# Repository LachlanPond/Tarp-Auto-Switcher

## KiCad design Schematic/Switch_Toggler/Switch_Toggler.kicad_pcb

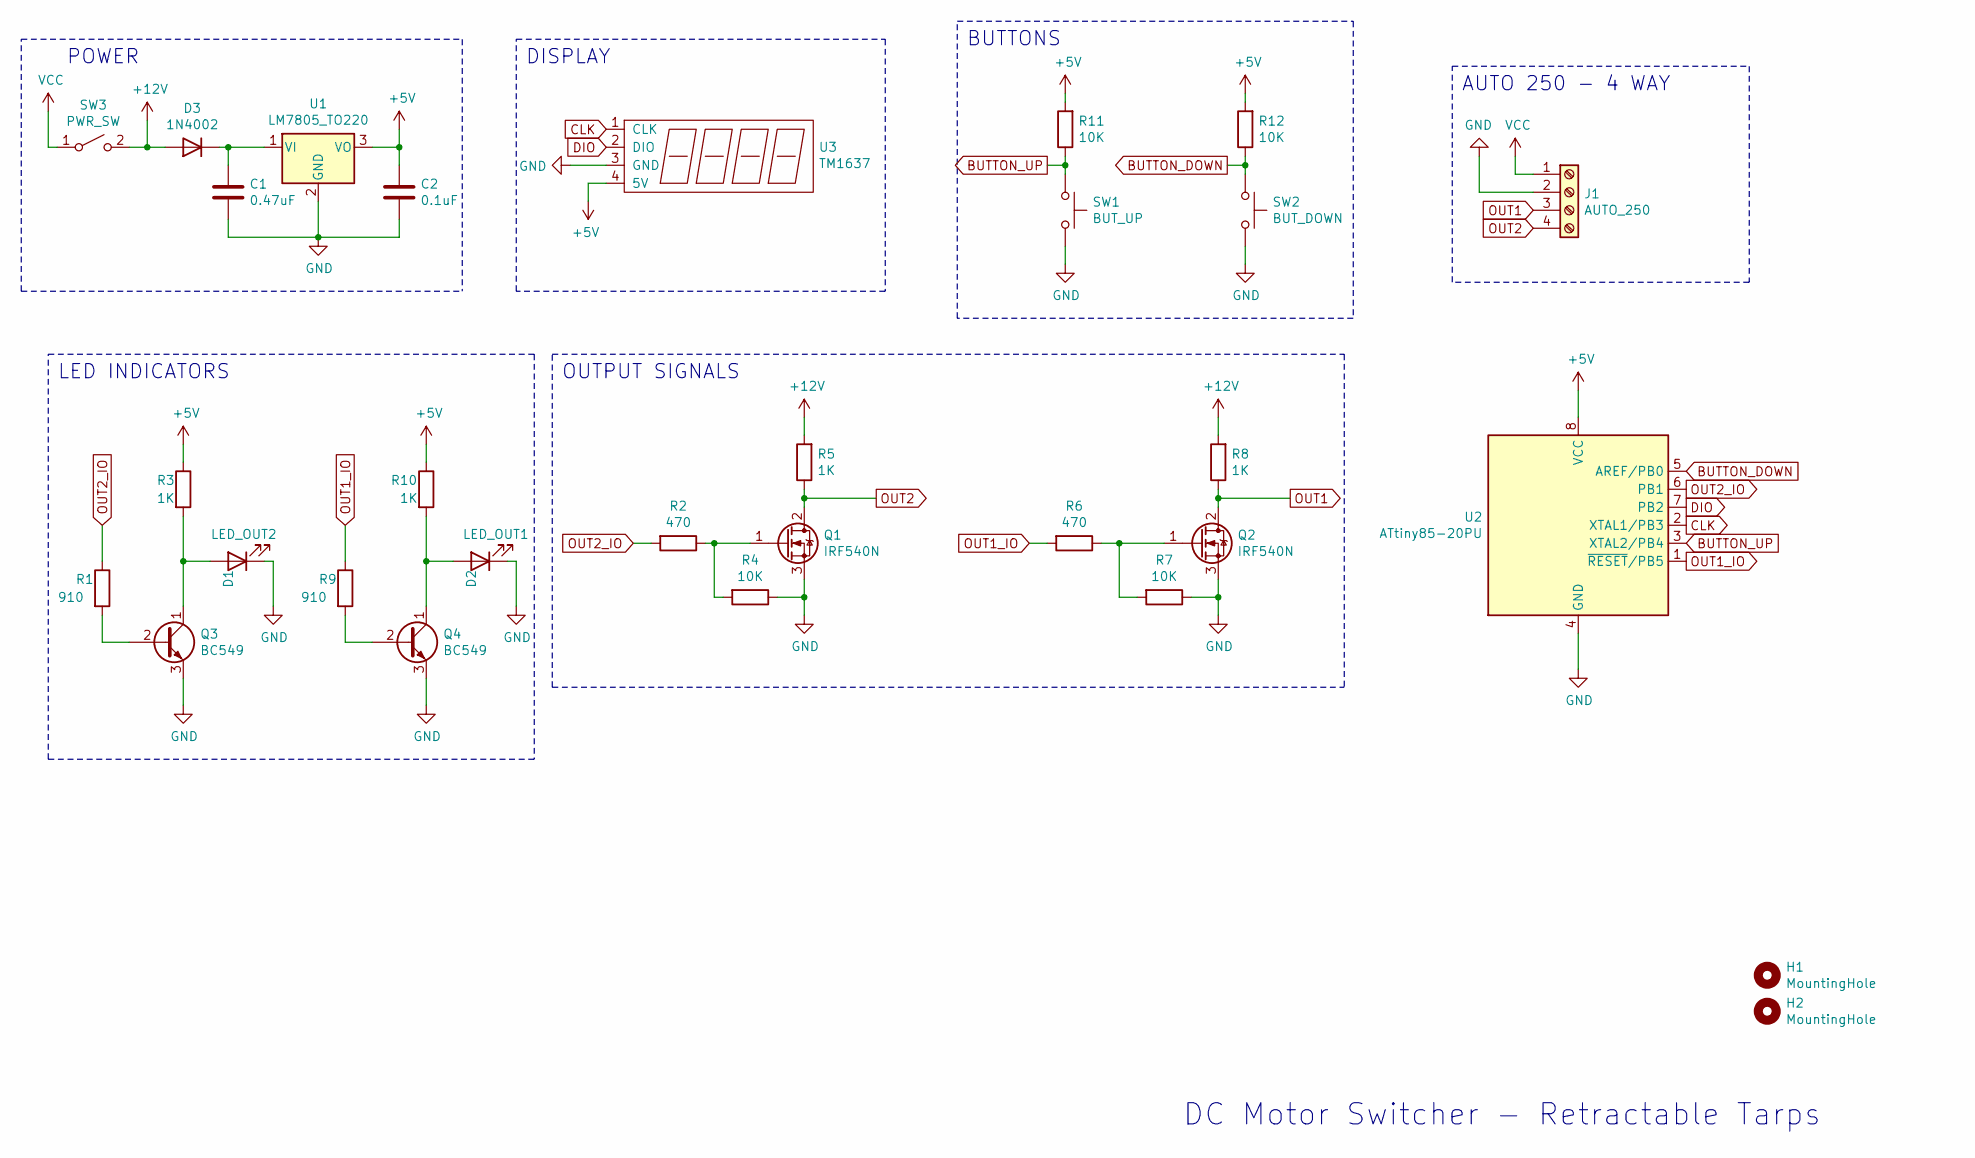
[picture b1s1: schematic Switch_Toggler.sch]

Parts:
C1: 0.47uF; C_Radial_D5.0mm_H11.0mm_P2.00mm
C2: 0.1uF; C_Radial_D5.0mm_H11.0mm_P2.00mm
D1: LED_OUT2; TerminalBlock_TE_282834-2_1x02_P2.54mm_Horizontal
D2: LED_OUT1; TerminalBlock_TE_282834-2_1x02_P2.54mm_Horizontal
D3: 1N4002; D_DO-41_SOD81_P10.16mm_Horizontal
H1, H2: MountingHole; MountingHole_3.2mm_M3_ISO7380
J1: AUTO_250; TerminalBlock_TE_282834-4_1x04_P2.54mm_Horizontal
Q1, Q2: IRF540N; TO-220-3_Vertical
Q3, Q4: BC549; TO-92_Inline
R1, R9: 910; R_Axial_DIN0204_L3.6mm_D1.6mm_P5.08mm_Horizontal
R2, R6: 470; R_Axial_DIN0207_L6.3mm_D2.5mm_P7.62mm_Horizontal
R3, R5, R8, R10: 1K; R_Axial_DIN0207_L6.3mm_D2.5mm_P7.62mm_Horizontal
R4, R7, R11, R12: 10K; R_Axial_DIN0207_L6.3mm_D2.5mm_P7.62mm_Horizontal
SW1: BUT_UP; TerminalBlock_TE_282834-2_1x02_P2.54mm_Horizontal
SW2: BUT_DOWN; TerminalBlock_TE_282834-2_1x02_P2.54mm_Horizontal
SW3: PWR_SW; TerminalBlock_TE_282834-2_1x02_P2.54mm_Horizontal
U1: LM7805_TO220; TO-220-3_Vertical
U2: ATtiny85-20PU; DIP-8_W7.62mm
U3: TM1637; TerminalBlock_TE_282834-4_1x04_P2.54mm_Horizontal

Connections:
+5V: C2.1, R3.1, R10.1, R11.2, R12.2, U1.3 (VO), U2.8 (VCC), U3.4 (5V)
+12V: D3.2 (A), R5.2, R8.2, SW3.2 (B)
BUTTON_DOWN: R12.1, SW2.1, U2.5 (AREF/PB0)
BUTTON_UP: R11.1, SW1.1, U2.3 (XTAL2/PB4)
CLK: U2.2 (XTAL1/PB3), U3.1 (CLK)
DIO: U2.7 (PB2), U3.2 (DIO)
GND: C1.2, C2.2, D1.1 (K), D2.1 (K), J1.2, Q1.3 (S), Q2.3 (S), Q3.3 (E), Q4.3 (E), R4.1, R7.1, SW1.2, SW2.2, U1.2 (GND), U2.4 (GND), U3.3 (GND)
unnamed: C1.1, D3.1 (K), U1.1 (VI)
unnamed: D1.2 (A), Q3.1 (C), R3.2
unnamed: D2.2 (A), Q4.1 (C), R10.2
unnamed: Q1.1 (G), R2.1, R4.2
unnamed: Q2.1 (G), R6.1, R7.2
unnamed: Q3.2 (B), R1.2
unnamed: Q4.2 (B), R9.2
OUT1: J1.3, Q2.2 (D), R8.1
OUT1_IO: R6.2, R9.1, U2.1 (~RESET~/PB5)
OUT2: J1.4, Q1.2 (D), R5.1
OUT2_IO: R1.1, R2.2, U2.6 (PB1)
VCC: J1.1, SW3.1 (A)

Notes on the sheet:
POWER
DISPLAY
BUTTONS
AUTO 250 - 4 WAY
OUTPUT SIGNALS
LED INDICATORS
DC Motor Switcher - Retractable Tarps

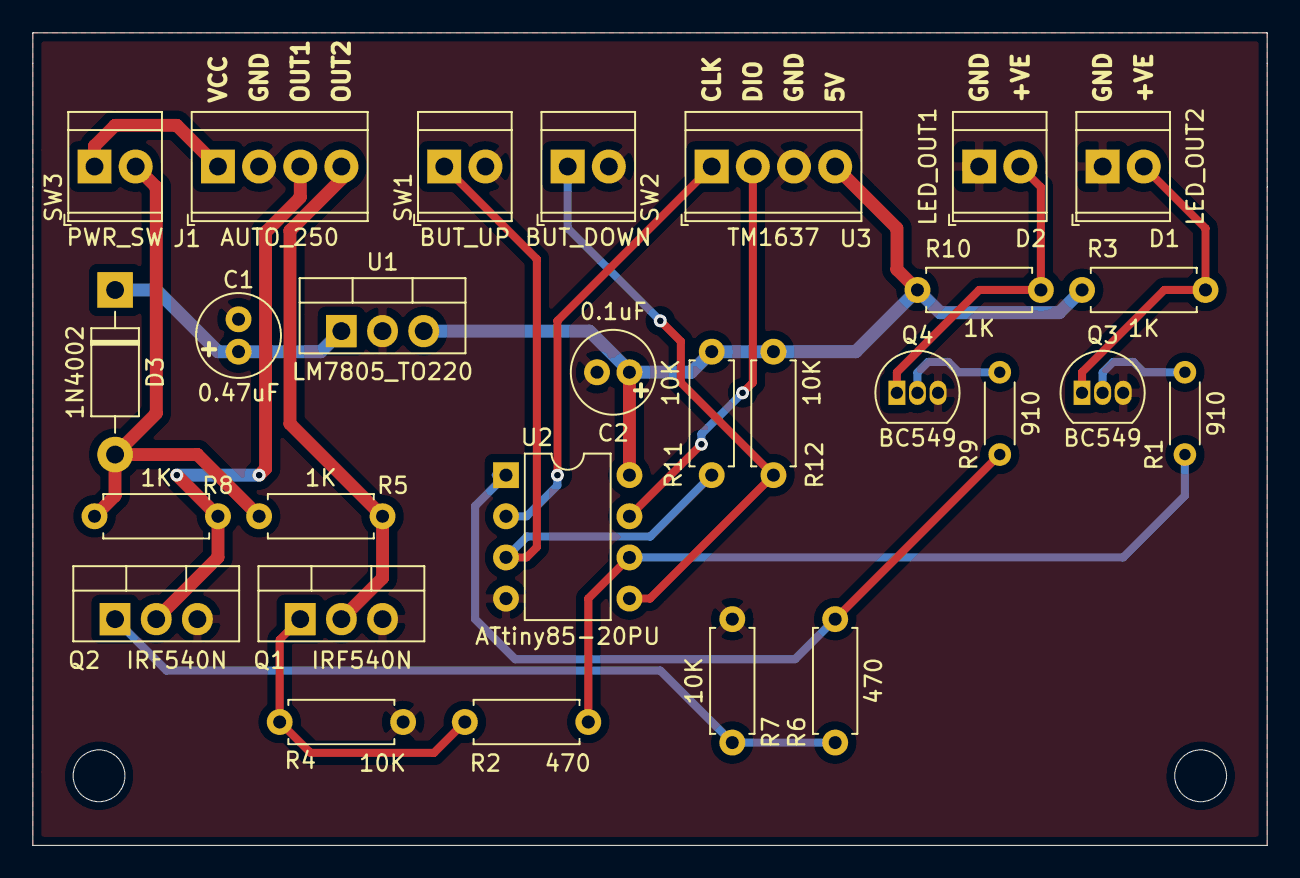
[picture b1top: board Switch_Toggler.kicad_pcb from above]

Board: 2 copper layers, 76.2 x 50.2 mm, 30 parts (0 on the bottom side), 19 nets.

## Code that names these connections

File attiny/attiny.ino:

#include "TM1637.h"
#include <EEPROM.h>
#define CLK 3
#define DIO 2
#define OUTPUT1 5
#define OUTPUT2 1
#define BUTTON_UP 4
#define BUTTON_DOWN 0
#define BUTTON_DB_DELAY 150
#define OUTPUT_ON_TIME 300

TM1637 Display(CLK,DIO);

unsigned long time;
unsigned long interval;
int addr = 1;
bool button_up_flag = false;
bool button_down_flag = false;
unsigned long button_up_last_pressed = 0;
unsigned long button_down_last_pressed = 0;
unsigned char output_toggle = 0;
unsigned long loop_time = 0;
unsigned long output1_pressed_timer = 0;
unsigned long output2_pressed_timer = 0;

void setup() {
  Display.init();
  Display.set(BRIGHT_TYPICAL);
  Display.point(1);

  pinMode(OUTPUT1, OUTPUT);
  pinMode(OUTPUT2, OUTPUT);
  pinMode(BUTTON_UP, INPUT);
  pinMode(BUTTON_DOWN, INPUT);
  delay(200);
  interval = EEPROM.read(addr);
  digitalWrite(OUTPUT1, LOW);
  digitalWrite(OUTPUT2, LOW);
}

void loop() {
  get_button_down_press();
  get_button_up_press();
  update_screen();
  handle_outputs();
}

void handle_outputs() {
  unsigned long next_time = millis() % (interval*1000);
  if (loop_time > next_time) {
    if (output_toggle) {
      digitalWrite(OUTPUT1, LOW);
      output1_pressed_timer = millis();
    }
    else {
      digitalWrite(OUTPUT2, LOW);
      output2_pressed_timer = millis();
    }
    output_toggle = !output_toggle;
  }
  loop_time = next_time;
  handle_turning_off_outputs();
}

void handle_turning_off_outputs() {
  if (output1_pressed_timer < millis() - OUTPUT_ON_TIME) {
    digitalWrite(OUTPUT1, HIGH);
  }
  if (output2_pressed_timer < millis() - OUTPUT_ON_TIME) {
    digitalWrite(OUTPUT2, HIGH);
  }
}

void update_screen() {
  int minutes = interval/60;
  int tens = (interval-minutes*60)/10;
  int singles = interval - (minutes*60) - (tens*10);
  Display.display(2, tens);
  Display.display(3, singles);
  Display.display(1, minutes);
}

void get_button_up_press() {
  if (!digitalRead(BUTTON_UP)) {
    if (button_up_last_pressed < millis() - BUTTON_DB_DELAY) {
      button_up_last_pressed = millis();
      if (interval < 120) {
        interval++;
        EEPROM.write(addr, interval);
      } 
    }
    loop_time = 0;
  }
}

void get_button_down_press() {
  if (!digitalRead(BUTTON_DOWN)) {
    if (button_down_last_pressed < millis() - BUTTON_DB_DELAY) {
      button_down_last_pressed = millis();
      if (interval > 1) {
        interval--;
        EEPROM.write(addr, interval);
      } 
    }
    loop_time = 0;
  }
}

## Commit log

2020-11-16 Initial version
2020-11-18 Turned on clock point, minute support, new 2min max, better button hold timer interaction
2020-11-19 Fixed overflow with interval variable
